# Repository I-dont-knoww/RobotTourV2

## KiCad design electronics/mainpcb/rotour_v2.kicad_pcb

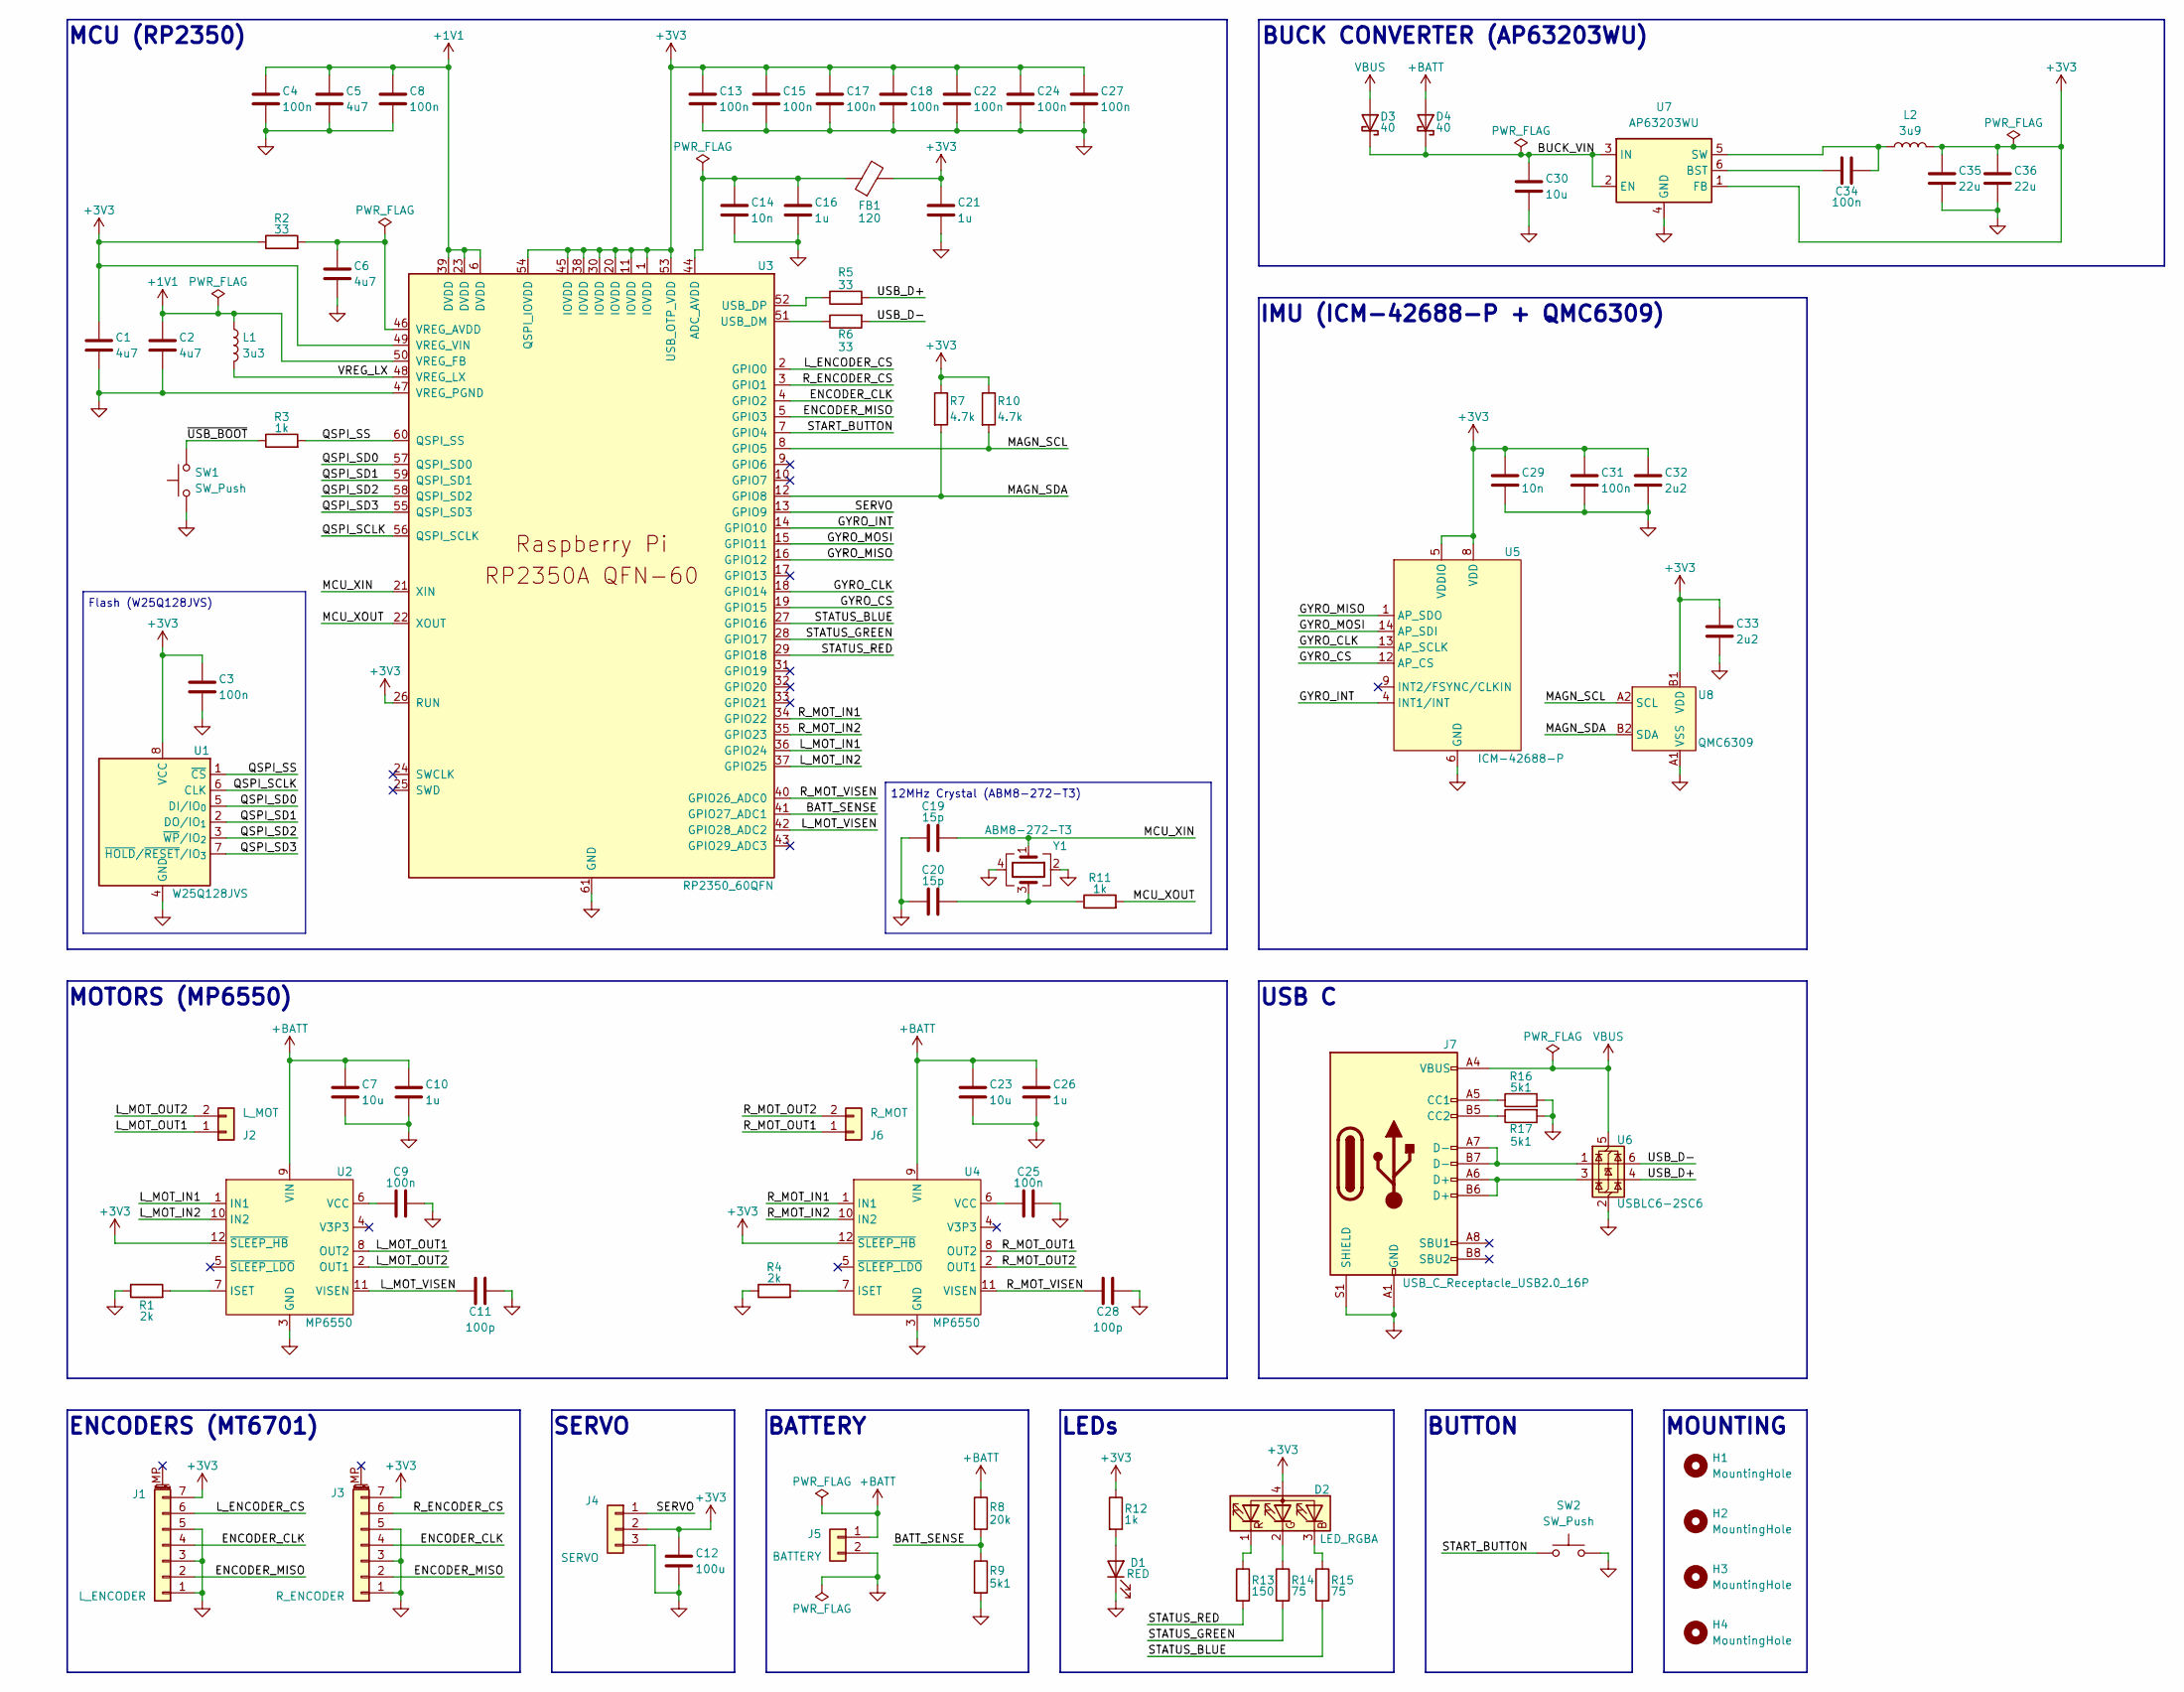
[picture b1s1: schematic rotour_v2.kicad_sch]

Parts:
C1, C2: 4u7; C_0402_1005Metric_small_pads
C3, C4, C8, C9, C13, C15, C17, C18, C22, C24, C25, C27, C31, C34: 100n; C_0402_1005Metric
C5, C6: 4u7; C_0402_1005Metric
C7, C23, C30: 10u; C_0603_1608Metric
C10, C16, C21, C26: 1u; C_0402_1005Metric
C11, C28: 100p; C_0402_1005Metric
C12: 100u; C_1206_3216Metric
C14, C29: 10n; C_0402_1005Metric
C19, C20: 15p; C_0402_1005Metric
C32, C33: 2u2; C_0402_1005Metric
C35, C36: 22u; C_0603_1608Metric
D1: RED; LED_0603_1608Metric
D2: LED_RGBA; LED_RGB_1210
D3, D4: 40; D_SOD-323
FB1: 120; L_0603_1608Metric
H1, H2, H3, H4: MountingHole; MountingHole_2.2mm_M2
J1: L_ENCODER; JST_SH_BM07B-SRSS-TB_1x07-1MP_P1.00mm_Vertical
J2: L_MOT; JST_XH_B2B-XH-A_1x02_P2.50mm_Vertical
J3: R_ENCODER; JST_SH_BM07B-SRSS-TB_1x07-1MP_P1.00mm_Vertical
J4: SERVO; PinHeader_1x03_P2.54mm_Vertical
J5: BATTERY; JST_VH_B2P-VH_1x02_P3.96mm_Vertical
J6: R_MOT; JST_XH_B2B-XH-A_1x02_P2.50mm_Vertical
J7: USB_C_Receptacle_USB2.0_16P; USB_C_Receptacle_GCT_USB4105-xx-A_16P_TopMnt_Horizontal
L1: 3u3; AOTA-B201610S3R3-101-T
L2: 3u9; L_Changjiang_FNR3012S
R1, R4: 2k; R_0402_1005Metric
R2, R5, R6: 33; R_0402_1005Metric
R3, R11, R12: 1k; R_0402_1005Metric
R7, R10: 4.7k; R_0402_1005Metric
R8: 20k; R_0603_1608Metric
R9, R16, R17: 5k1; R_0402_1005Metric
R13: 150; R_0603_1608Metric
R14, R15: 75; R_0603_1608Metric
SW1, SW2: SW_Push; SW_TS-1088-AR02016
U1: W25Q128JVS; SOIC-8_5.3x5.3mm_P1.27mm
U2, U4: MP6550
U3: RP2350_60QFN; QFN-60-1EP_7x7mm_P0.4mm_EP3.4x3.4mm_ThermalVias
U5: ICM-42688-P; ICM42688P
U6: USBLC6-2SC6; SOT-23-6
U7: AP63203WU; TSOT-23-6
U8: QMC6309
Y1: ABM8-272-T3; Crystal_SMD_3225-4Pin_3.2x2.5mm

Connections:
+1V1: C2.1, C4.1, C5.1, C8.1, L1.1, U3.6 (DVDD), U3.23 (DVDD), U3.39 (DVDD), U3.50 (VREG_FB)
+3V3: C1.1, C3.1, C12.1, C13.1, C15.1, C17.1, C18.1, C21.1, C22.1, C24.1, C27.1, C29.1, C31.1, C32.1, C33.1, C35.1, C36.1, D2.4 (A), FB1.2, J1.7, J3.7, J4.2, L2.2, R2.1, R7.1, R10.1, R12.1, U1.8 (VCC), U2.12 (~SLEEP_HB), U3.1 (IOVDD), U3.11 (IOVDD), U3.20 (IOVDD), U3.26 (RUN), U3.30 (IOVDD), U3.38 (IOVDD), U3.45 (IOVDD), U3.49 (VREG_VIN), U3.53 (USB_OTP_VDD), U3.54 (QSPI_IOVDD), U4.12 (~SLEEP_HB), U5.5 (VDDIO), U5.8 (VDD), U7.1 (FB), U8.B1 (VDD)
+BATT: C7.1, C10.1, C23.1, C26.1, D4.2 (A), J5.1, R8.1, U2.9 (VIN), U4.9 (VIN)
/BATT_SENSE: R8.2, R9.1, U3.41 (GPIO27_ADC1)
/BUCK_VIN: C30.1, D3.1 (K), D4.1 (K), U7.2 (EN), U7.3 (IN)
/ENCODER_CLK: J1.4, J3.4, U3.4 (GPIO2)
/ENCODER_MISO: J1.2, J3.2, U3.5 (GPIO3)
/GYRO_CLK: U3.18 (GPIO14), U5.13 (AP_SCLK)
/GYRO_CS: U3.19 (GPIO15), U5.12 (AP_CS)
/GYRO_INT: U3.14 (GPIO10), U5.4 (INT1/INT)
/GYRO_MISO: U3.16 (GPIO12), U5.1 (AP_SDO)
/GYRO_MOSI: U3.15 (GPIO11), U5.14 (AP_SDI)
/L_ENCODER_CS: J1.6, U3.2 (GPIO0)
/L_MOT_IN1: U2.1 (IN1), U3.36 (GPIO24)
/L_MOT_IN2: U2.10 (IN2), U3.37 (GPIO25)
/L_MOT_OUT1: J2.1, U2.8 (OUT2)
/L_MOT_OUT2: J2.2, U2.2 (OUT1)
/L_MOT_VISEN: C11.1, U2.11 (VISEN), U3.42 (GPIO28_ADC2)
/MAGN_SCL: R10.2, U3.8 (GPIO5), U8.A2 (SCL)
/MAGN_SDA: R7.2, U3.12 (GPIO8), U8.B2 (SDA)
/MCU_XIN: C19.2, U3.21 (XIN), Y1.1
/MCU_XOUT: R11.2, U3.22 (XOUT)
/QSPI_SCLK: U1.6 (CLK), U3.56 (QSPI_SCLK)
/QSPI_SD0: U1.5 (DI/IO_{0}), U3.57 (QSPI_SD0)
/QSPI_SD1: U1.2 (DO/IO_{1}), U3.59 (QSPI_SD1)
/QSPI_SD2: U1.3 (~WP/IO_{2}), U3.58 (QSPI_SD2)
/QSPI_SD3: U1.7 (~HOLD/~RESET/IO_{3}), U3.55 (QSPI_SD3)
/QSPI_SS: R3.2, U1.1 (~CS), U3.60 (QSPI_SS)
/R_ENCODER_CS: J3.6, U3.3 (GPIO1)
/R_MOT_IN1: U3.34 (GPIO22), U4.1 (IN1)
/R_MOT_IN2: U3.35 (GPIO23), U4.10 (IN2)
/R_MOT_OUT1: J6.1, U4.8 (OUT2)
/R_MOT_OUT2: J6.2, U4.2 (OUT1)
/R_MOT_VISEN: C28.1, U3.40 (GPIO26_ADC0), U4.11 (VISEN)
/SERVO: J4.1, U3.13 (GPIO9)
/START_BUTTON: SW2.1, U3.7 (GPIO4)
/STATUS_BLUE: R15.2, U3.27 (GPIO16)
/STATUS_GREEN: R14.2, U3.28 (GPIO17)
/STATUS_RED: R13.2, U3.29 (GPIO18)
/USB_D+: R5.2, U6.4 (I/O2)
/USB_D-: R6.2, U6.6 (I/O1)
/VREG_LX: L1.2, U3.48 (VREG_LX)
/~USB_BOOT: R3.1, SW1.2
GND: C1.2, C2.2, C3.2, C4.2, C5.2, C6.2, C7.2, C8.2, C9.2, C10.2, C11.2, C12.2, C13.2, C14.2, C15.2, C16.2, C17.2, C18.2, C19.1, C20.1, C21.2, C22.2, C23.2, C24.2, C25.2, C26.2, C27.2, C28.2, C29.2, C30.2, C31.2, C32.2, C33.2, C35.2, C36.2, D1.1 (K), J1.1, J1.3, J1.5, J3.1, J3.3, J3.5, J4.3, J5.2, J7.A1 (GND), J7.A12 (GND), J7.B1 (GND), J7.B12 (GND), J7.S1 (SHIELD), R1.1, R4.1, R9.2, R16.2, R17.2, SW1.1, SW2.2, U1.4 (GND), U2.3 (GND), U3.47 (VREG_PGND), U3.61 (GND), U4.3 (GND), U5.6 (GND), U5.7 (RESV), U5.11 (RESV), U6.2 (GND), U7.4 (GND), U8.A1 (VSS), Y1.2, Y1.4
unnamed: C20.2, R11.1, Y1.3
unnamed: D1.2 (A), R12.2
unnamed: D2.3 (BK), R15.1
unnamed: D2.2 (GK), R14.1
unnamed: D2.1 (RK), R13.1
unnamed: J7.A5 (CC1), R16.1
unnamed: J7.B5 (CC2), R17.1
unnamed: J7.A6 (D+), J7.B6 (D+), U6.3 (I/O2)
unnamed: J7.A7 (D-), J7.B7 (D-), U6.1 (I/O1)
unnamed: R1.2, U2.7 (ISET)
unnamed: C9.1, U2.6 (VCC)
unnamed: C14.1, C16.1, FB1.1, U3.44 (ADC_AVDD)
unnamed: R6.1, U3.51 (USB_DM)
unnamed: R5.1, U3.52 (USB_DP)
unnamed: C6.1, R2.2, U3.46 (VREG_AVDD)
unnamed: R4.2, U4.7 (ISET)
unnamed: C25.1, U4.6 (VCC)
unnamed: C34.2, U7.6 (BST)
unnamed: C34.1, L2.1, U7.5 (SW)
VBUS: D3.2 (A), J7.A4 (VBUS), J7.A9 (VBUS), J7.B4 (VBUS), J7.B9 (VBUS), U6.5 (VBUS)

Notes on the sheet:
BUCK CONVERTER (AP63203WU)
USB C
IMU (ICM-42688-P + QMC6309)
ENCODERS (MT6701)
BUTTON
MOTORS (MP6550)
SERVO
Flash (W25Q128JVS)
LEDs
MCU (RP2350)
12MHz Crystal (ABM8-272-T3)
BATTERY
MOUNTING

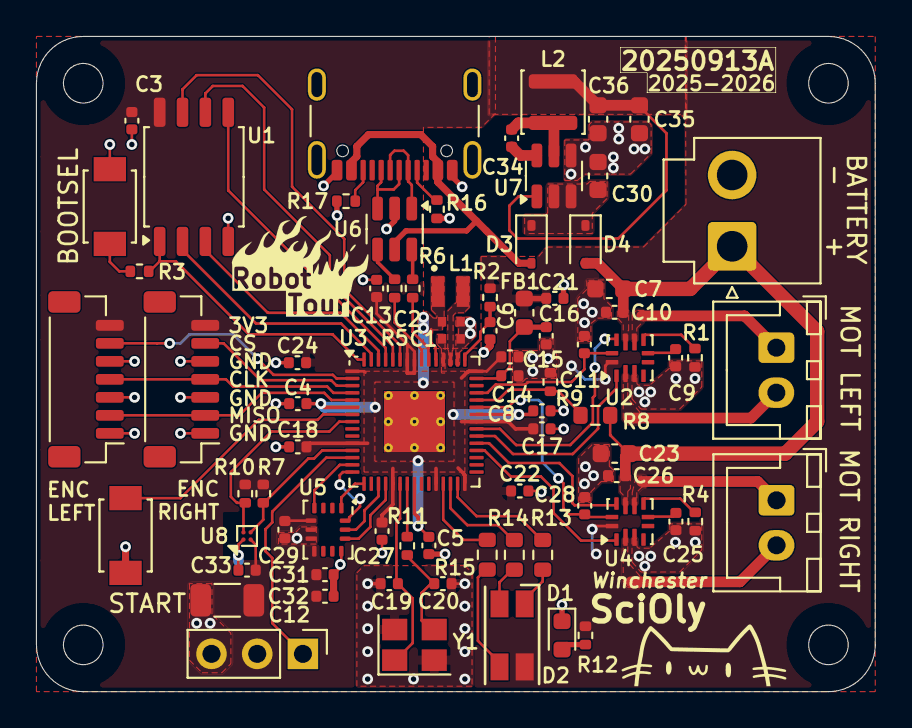
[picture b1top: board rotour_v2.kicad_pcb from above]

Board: 2 copper layers, 46.6 x 36.4 mm, 82 parts (0 on the bottom side), 64 nets.

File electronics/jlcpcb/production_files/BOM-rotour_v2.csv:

Comment,Designator,Footprint,LCSC,Quantity
1k,"R11,R12,R3",R_0402_1005Metric,C11702,3
2u2,"C32,C33",C_0402_1005Metric,C12530,2
USB_C_Receptacle_USB2.0_16P,J7,USB_C_Receptacle_GCT_USB4105-xx-A_16P_TopMnt_Horizontal,C136423,1
120,FB1,L_0603_1608Metric,C14709,1
100u,C12,C_1206_3216Metric,C15008,1
10n,"C14,C29",C_0402_1005Metric,C15195,2
100n,"C13,C15,C17,C18,C22,C24,C25,C27,C3,C31,C34,C4,C8,C9",C_0402_1005Metric,C1525,14
100p,"C11,C28",C_0402_1005Metric,C1546,2
15p,"C19,C20",C_0402_1005Metric,C1548,2
L_MOT,"J2,J6",JST_XH_B2B-XH-A_1x02_P2.50mm_Vertical,C158012,2
BATTERY,J5,JST_VH_B2P-VH_1x02_P3.96mm_Vertical,C160315,1
L_ENCODER,"J1,J3",JST_SH_BM07B-SRSS-TB_1x07-1MP_P1.00mm_Vertical,C160393,2
3u9,L2,L_Changjiang_FNR3012S,C167751,1
ICM-42688-P,U5,ICM42688P,C1850418,1
40,"D3,D4",D_SOD-323,C191023,2
ABM8-272-T3,Y1,Crystal_SMD_3225-4Pin_3.2x2.5mm,C20625731,1
150,R13,R_0603_1608Metric,C22808,1
RED,D1,LED_0603_1608Metric,C2286,1
4u7,"C1,C2,C5,C6",C_0402_1005Metric_small_pads,C23733,4
33,"R2,R5,R6",R_0402_1005Metric,C25105,3
4.7k,"R10,R7",R_0402_1005Metric,C25900,2
5k1,"R16,R17,R9",R_0402_1005Metric,C25905,3
MP6550,"U2,U4",MP6550,C3681248,2
2k,"R1,R4",R_0402_1005Metric,C4109,2
20k,R8,R_0603_1608Metric,C4184,1
RP2350_60QFN,U3,QFN-60-1EP_7x7mm_P0.4mm_EP3.4x3.4mm_ThermalVias,C42411118,1
3u3,L1,AOTA-B201610S3R3-101-T,C42411119,1
SERVO,J4,PinHeader_1x03_P2.54mm_Vertical,C42431831,1
75,"R14,R15",R_0603_1608Metric,C4275,2
1u,"C10,C16,C21,C26",C_0402_1005Metric,C52923,4
QMC6309,U8,QMC6309,C5439871,1
22u,"C35,C36",C_0603_1608Metric,C59461,2
SW_Push,"SW1,SW2",SW_TS-1088-AR02016,C720477,2
USBLC6-2SC6,U6,SOT-23-6,C7519,1
AP63203WU,U7,TSOT-23-6,C780769,1
10u,"C23,C30,C7",C_0603_1608Metric,C96446,3
LED_RGBA,D2,LED_RGB_1210,C965844,1
W25Q128JVS,U1,SOIC-8_5.3x5.3mm_P1.27mm,C97521,1

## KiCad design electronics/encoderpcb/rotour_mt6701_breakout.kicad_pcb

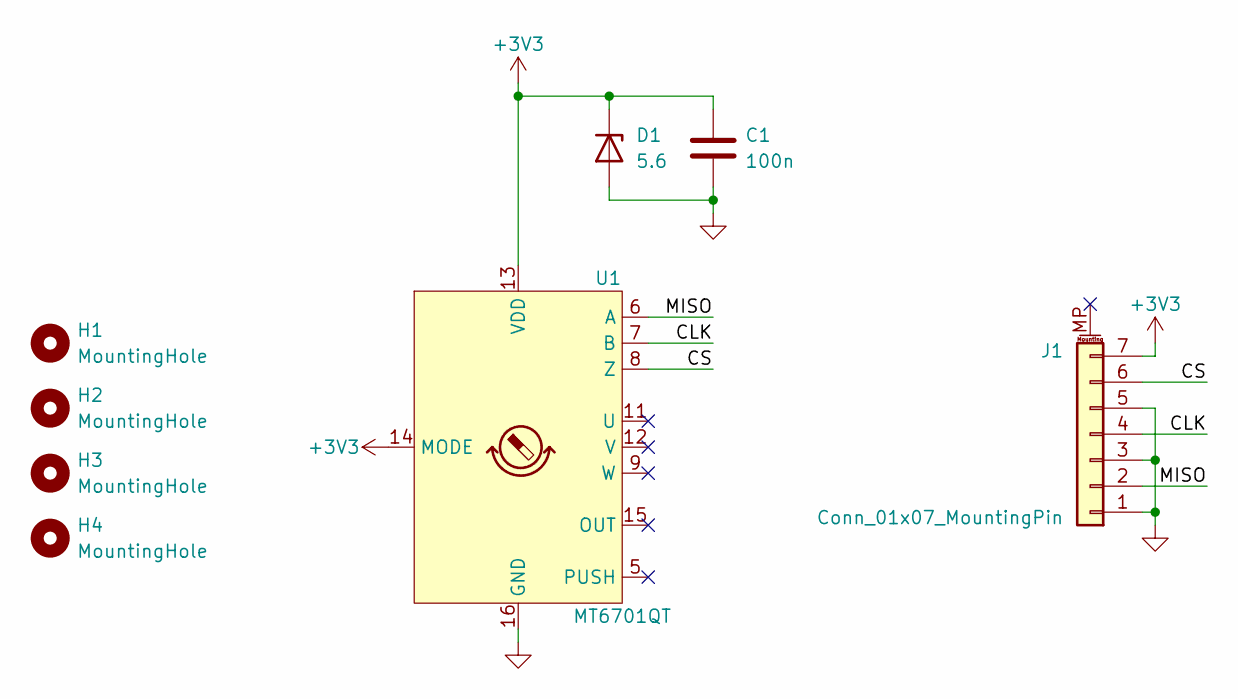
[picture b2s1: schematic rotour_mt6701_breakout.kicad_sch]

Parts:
C1: 100n; C_0402_1005Metric
D1: 5.6; D_SOD-123
H1, H2, H3, H4: MountingHole; MountingHole_2.2mm_M2
J1: Conn_01x07_MountingPin; JST_SH_SM07B-SRSS-TB_1x07-1MP_P1.00mm_Horizontal
U1: MT6701QT; QFN-16-1EP_3x3mm_P0.5mm_EP1.7x1.7mm

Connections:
+3V3: C1.1, D1.1 (K), J1.7, U1.13 (VDD), U1.14 (MODE)
/CLK: J1.4, U1.7 (B)
/CS: J1.6, U1.8 (Z)
/MISO: J1.2, U1.6 (A)
GND: C1.2, D1.2 (A), J1.1, J1.3, J1.5, U1.16 (GND), U1.17 (GND)

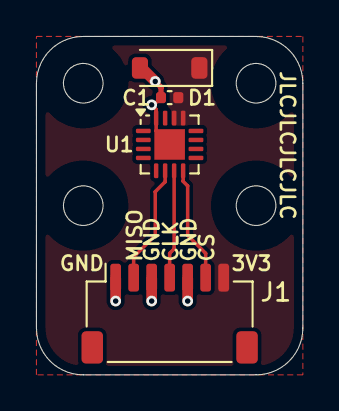
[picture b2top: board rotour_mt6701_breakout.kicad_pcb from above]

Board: 2 copper layers, 14.8 x 18.8 mm, 8 parts (1 on the bottom side), 5 nets.

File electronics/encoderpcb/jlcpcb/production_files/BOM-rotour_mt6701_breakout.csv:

Comment,Designator,Footprint,LCSC,Quantity
100n,C1,C_0402_1005Metric,C1525,1
Conn_01x07_MountingPin,J1,JST_SH_SM07B-SRSS-TB_1x07-1MP_P1.00mm_Horizontal,C160406,1
5.6,D1,D_SOD-123,C19077402,1
MT6701QT,U1,QFN-16-1EP_3x3mm_P0.5mm_EP1.7x1.7mm,C2913974,1

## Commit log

2025-10-01 ignore .vscode
2025-10-03 pio i2c for compass
2025-10-05 moved forward kinematics onto core1 and now using repeating_timer to time the sampling
2025-10-10 mostly finished
2025-10-26 turning with stanley but its lowk fucked rn
2025-11-07 sorta fixed turning
2025-11-08 tuning changes also better ahk script
2025-11-09 added offsets but arent tested yet
2025-11-11 updated straight.cpp to avoid the jerking movement on non-90 deg turns and updated follower to fix max path length being 102 somehow.
2025-11-12 delayed measurement of final position until after a set time
2025-11-12 made it calibrate the current sensing bias because we are totally using that right now
2025-11-14 turning should allocate more target time now
2025-11-14 fixed time allocation to dedicated turns
2025-11-16 cornell approved edition
2025-11-17 fixed fast loop and slow loop dt being slightly off
2025-11-24 moved target time calculations into a namespace, moved forward kinematics update into several lines, fully stopped using encoders for position updates, fixed small bug in limiting battery voltage in 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
2025-11-29 moved around final status print stuff and made it print final angle as well now
2025-11-29 fixed print statement
2025-11-29 theoretically stopped passing dt through function calls and now only passes through constructors. this should not have changed any behaviors
2025-12-15 changed slowdown speed to be calculated from the sqrt of distance to allow for lower slowdownKs
2025-12-15 Commit from Henry's laptop after WSSL
2025-12-15 telemetry added for centripetal limiting
2025-12-15 first time getting centripetal limit to work
2025-12-16 centripetal limiting telemetry and also sorta fixed
2025-12-16 final tuning and testing of centripetal limiting before test at track
2025-12-16 added failed run feature
2025-12-16 updated competition.ahk to be able to combine previous commands with backtick key
2025-12-17 added a filter to the centripetal limit so that there is less jerkiness in linear velocity when centripetal limiting matters
2025-12-17 clamped filteredmaxlinearspeed so that nothing goofy happens when maxLinearSpeed is too high for too long
2025-12-19 fixed compiler to handle reverse 90 degree turns correctly
2025-12-20 changed grabbing speed to be a constant
2026-01-05 made ForwardKinematics state zero initialized because I have NO CLUE how that was even compiling before like hello
2026-01-05 added electronics folder
2026-01-05 added encoderpcb to electronics folder
2026-01-08 thin wheel rt new constants
2026-01-10 fixed fakeout holy cow the solution was so simple what the actual heck
2026-01-11 jk the solution was a bit more advanced but now its fr dealt with, idk abt completely fixed tho
2026-01-11 switched to std::atomic instead of weird user defined atomic after confirming std::atomic lowk works
2026-01-12 cleaned up a few weird lines of code, should still work the same
2026-01-14 removed random comment saying 8.3cm
2026-01-14 implemented new alg for speed, something is not working down the line
2026-01-14 fixed some goofy ahh bug where there was this problem with an AController in the velocity regulator, goofy coz were not freakin using the A Controller. also reduced slowdownkp to demonstrate POWER of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
2026-01-17 updated atan2 implementation to actually work
2026-01-18 sort of fixed weird stopping at lower speeds, though the solution is super goofy
2026-01-19 ok lowk genuinely fixed all those goofy centripetal problems
2026-01-19 pre-mit tuning
2026-01-22 changed centripetal thing
2026-01-31 moved competition to include folder, shifted out command and path into separate files. command compiles into path using Accumulate.hpp, which is "owned" by the Path namespace
2026-02-05 finished all compile time items
2026-02-07 sorta did it? soooo sooo many bugs i rlly need this on ev tho
2026-02-11 Innovation challenge ahk for umass
2026-02-14 innovation award changes
2026-02-26 made it so that LAST_MOVE takes into account the offset of the move when calculating the new target position
2026-02-26 computed wheel radius
2026-02-26 changed wheel radius
2026-02-26 switched motor signs so ts actually runs properly
2026-03-04 tentative acceleration changes
2026-03-05 tentative gyroscope filtering
2026-03-05 tentative changes to in place rotation slowdown accleration
2026-03-05 tentative changes for speed up acceleration in place rotation
2026-03-07 likely fixed most bugs with speedup acceleration for both straight and rotation
2026-03-07 updated dowel distance
2026-03-31 updated electronics to kicad 10
2026-04-16 code right after states!
2026-04-16 updated pcb 3d models
